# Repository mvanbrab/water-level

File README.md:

# Introduction
Here I share hardware and software about my **water-level** project,
whose purpose is to measure the water level in a water reservoir,
located under the ground.

This project actually has a predecessor. Enjoy reading about it in this [bit of history](doc/history.md).

# The transmitter
The first piece of hardware is a transmitter.
It measures the water level with a waterproof ultrasonic sensor and sends the measurement result as a JSON object via RS232 to a possibly connected receiver.

The positioning of this sensor in my project is described in the [physical setup](doc/physical.md).

Here are some [pictures](doc/pictures-transmitter.md) showing the transmitter in practice.

In the folder **hardware/transmitter** you'll find the hardware design as a [KiCad](https://www.kicad.org/) project.
Without Kicad installed, you can view
- [the schematic diagram as .pdf](../master/hardware/transmitter.pdf);
- [the copper layout of the printed circuit board](../master/hardware/transmitter_cu.pdf);
- [the component placement on the printed circuit board](../master/hardware/transmitter_silk.pdf).

The folder **software/WaterLevelTransmitter** is an [Arduino](https://www.arduino.cc/) sketch, containing the software of the transmitter part of the project.

Read more about this piece of software [here](doc/water-level-transmitter-software.md).

# The receiver
The second piece of hardware is the receiver.
It requests output from the transmitter and publishes is to whatever destination.

Here are some [pictures](doc/pictures-receiver.md) showing the receiver in practice.

In the folder **hardware/receiver** you'll find the hardware design as a [KiCad](https://www.kicad.org/) project.
Without Kicad installed, you can view
- [the schematic diagram as .pdf](../master/hardware/receiver.pdf);
- [the copper layout of the printed circuit board](../master/hardware/receiver_cu.pdf);
- [the component placement on the printed circuit board](../master/hardware/receiver_silk.pdf).

About the receiver hardware:
- the RS232 level converter is the same as used for the transmitter, this time it is powered from 3V3;
- the character-based LCD screen to connect is a 2 rows of 16 columns type, using an HD44780 driver, connected via I2C @ 3V3, but powered @ 5V;
- the processor board (chosen because of its WiFi connectivity) is a [ESP32 DevKitC](https://docs.espressif.com/projects/esp-idf/en/latest/esp32/hw-reference/esp32/get-started-devkitc.html)
 (with ESP32-WROOM-32D module).

The folder **software/WaterLevelReceivers** is contains a set of [Arduino](https://www.arduino.cc/) sketches, each containing a different software solution for the receiver part of the project.

Read more about this piece of software [here](doc/water-level-receiver-software.md).

# Connecting the transmitter with the receiver

| Transmitter | Receiver   |
| ----------- | ---------- |
| GND (J1.2)  | GND (J1.3) |
| TXD (J1.4)  | RXD (J1.2) |
| RXD (J1.5)  | TXD (J1.1) |

# Lessons learned
[The temperature measurement](doc/ll01.md)

[Condensation on the sensor](doc/ll02.md)

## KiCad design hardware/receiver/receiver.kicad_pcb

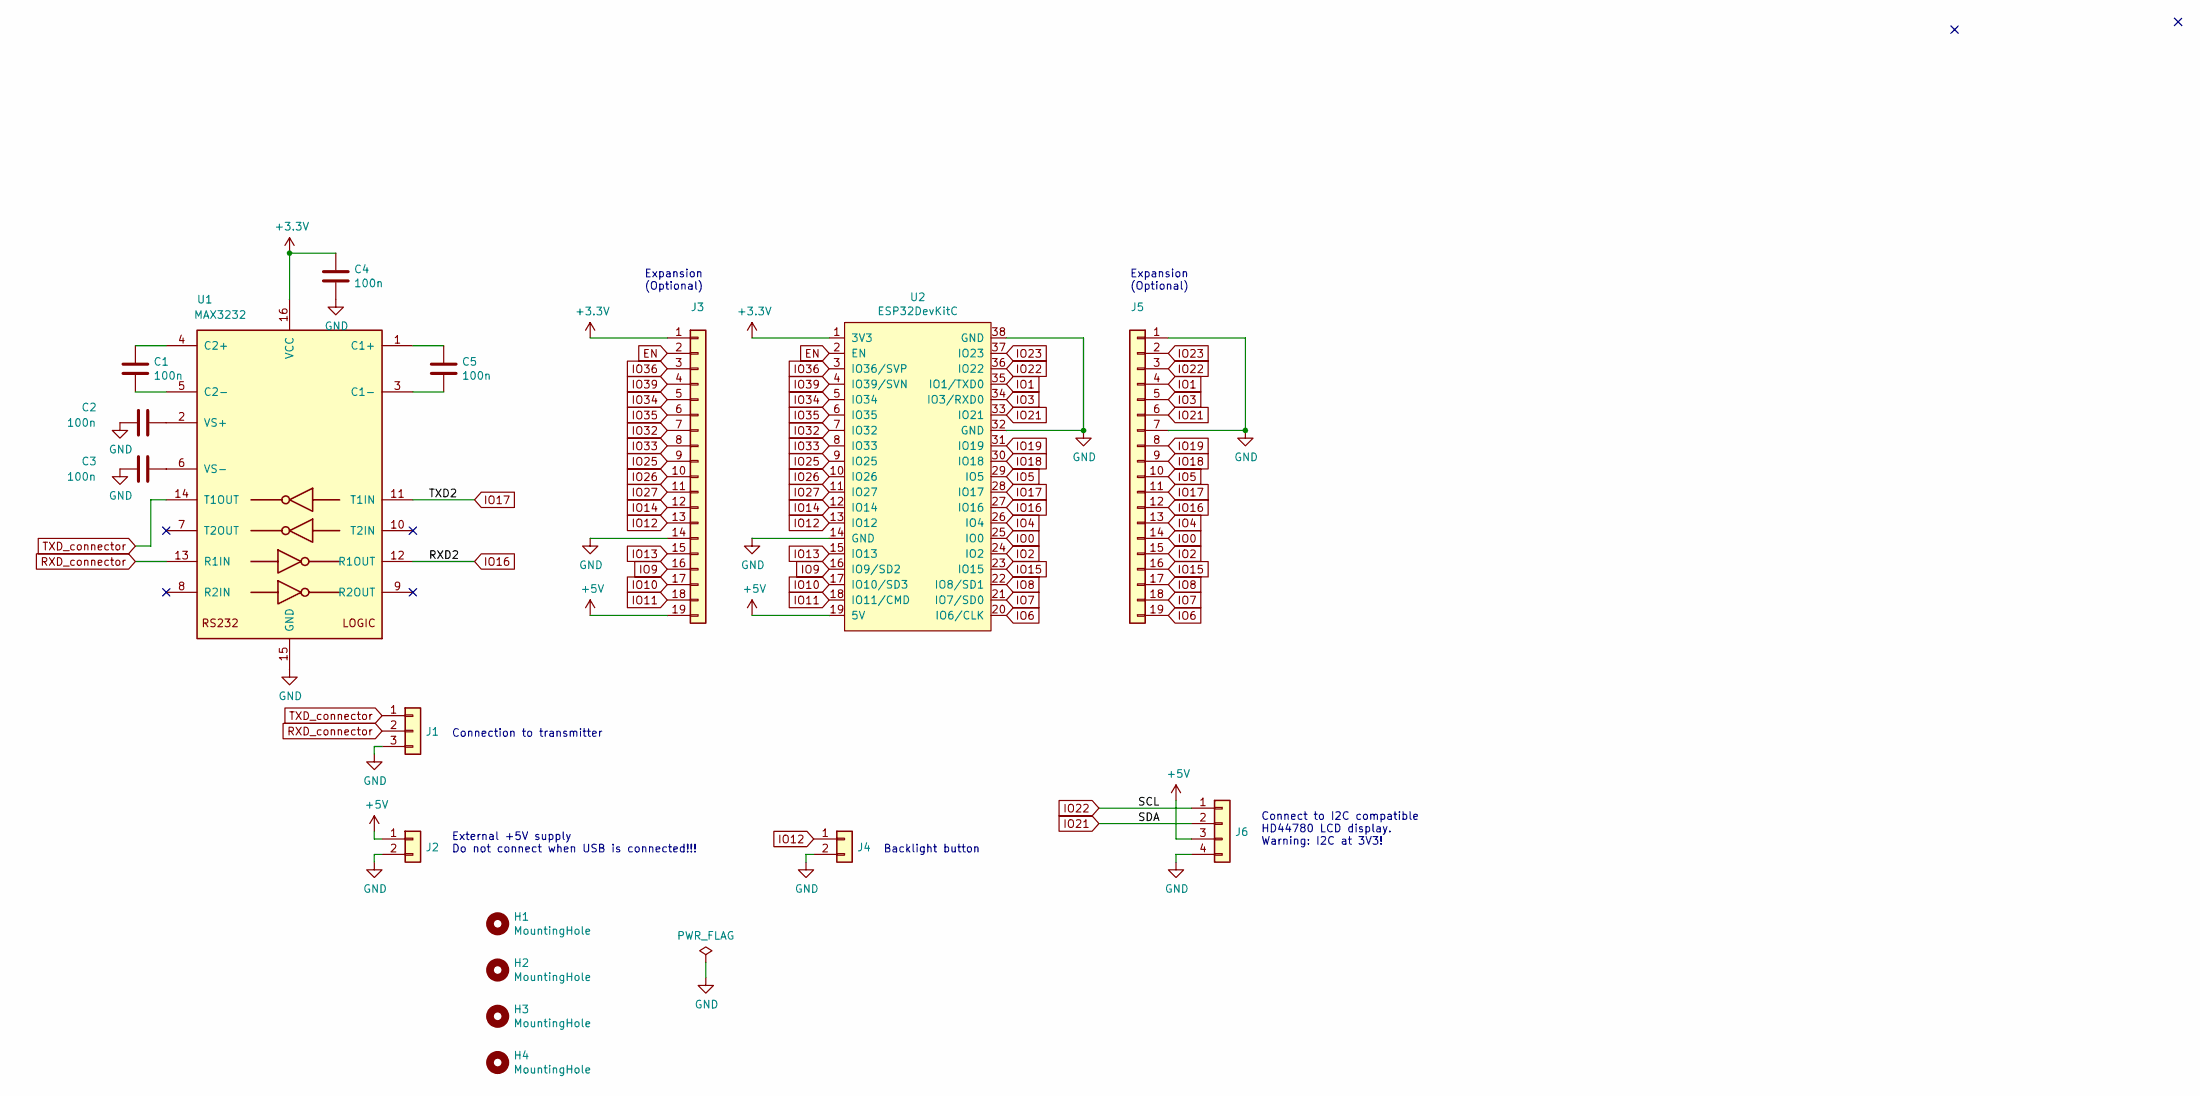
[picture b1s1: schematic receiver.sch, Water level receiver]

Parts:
C1, C2, C3, C4, C5: 100n; C_Rect_L7.0mm_W2.0mm_P5.00mm
H1, H2, H3, H4: MountingHole; MountingHole_3.2mm_M3
J1: Conn_01x03; PinHeader_1x03_P2.54mm_Vertical
J2, J4: Conn_01x02; PinHeader_1x02_P2.54mm_Vertical
J3, J5: Conn_01x19; PinHeader_1x19_P2.54mm_Vertical
J6: Conn_01x04; PinHeader_1x04_P2.54mm_Vertical
U1: MAX3232; DIP-16_W7.62mm_LongPads
U2: ESP32DevKitC; DIP-38_W25.4mm

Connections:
+3V3: C4.1, J3.1, U1.16 (VCC), U2.1 (3V3)
+5V: J2.1, J3.19, J6.3, U2.19 (5V)
EN: J3.2, U2.2 (EN)
GND: C2.2, C3.2, C4.2, J1.3, J2.2, J3.14, J4.2, J5.1, J5.7, J6.4, U1.15 (GND), U2.14 (GND), U2.32 (GND), U2.38 (GND)
IO0: J5.14, U2.25 (IO0)
IO1: J5.4, U2.35 (IO1/TXD0)
IO2: J5.15, U2.24 (IO2)
IO3: J5.5, U2.34 (IO3/RXD0)
IO4: J5.13, U2.26 (IO4)
IO5: J5.10, U2.29 (IO5)
IO6: J5.19, U2.20 (IO6/CLK)
IO7: J5.18, U2.21 (IO7/SD0)
IO8: J5.17, U2.22 (IO8/SD1)
IO9: J3.16, U2.16 (IO9/SD2)
IO10: J3.17, U2.17 (IO10/SD3)
IO11: J3.18, U2.18 (IO11/CMD)
IO12: J3.13, J4.1, U2.13 (IO12)
IO13: J3.15, U2.15 (IO13)
IO14: J3.12, U2.12 (IO14)
IO15: J5.16, U2.23 (IO15)
IO16: J5.12, U1.12 (R1OUT), U2.27 (IO16)
IO17: J5.11, U1.11 (T1IN), U2.28 (IO17)
IO18: J5.9, U2.30 (IO18)
IO19: J5.8, U2.31 (IO19)
IO21: J5.6, J6.2, U2.33 (IO21)
IO22: J5.3, J6.1, U2.36 (IO22)
IO23: J5.2, U2.37 (IO23)
IO25: J3.9, U2.9 (IO25)
IO26: J3.10, U2.10 (IO26)
IO27: J3.11, U2.11 (IO27)
IO32: J3.7, U2.7 (IO32)
IO33: J3.8, U2.8 (IO33)
IO34: J3.5, U2.5 (IO34)
IO35: J3.6, U2.6 (IO35)
IO36: J3.3, U2.3 (IO36/SVP)
IO39: J3.4, U2.4 (IO39/SVN)
unnamed: C1.1, U1.4 (C2+)
unnamed: C1.2, U1.5 (C2-)
unnamed: C2.1, U1.2 (VS+)
unnamed: C3.1, U1.6 (VS-)
unnamed: C5.1, U1.1 (C1+)
unnamed: C5.2, U1.3 (C1-)
RXD_connector: J1.2, U1.13 (R1IN)
TXD_connector: J1.1, U1.14 (T1OUT)

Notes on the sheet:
Connect to I2C compatible HD44780 LCD display. Warning: I2C at 3V3!
External +5V supply Do not connect when USB is connected!!!
Connection to transmitter
Expansion (Optional)
Backlight button

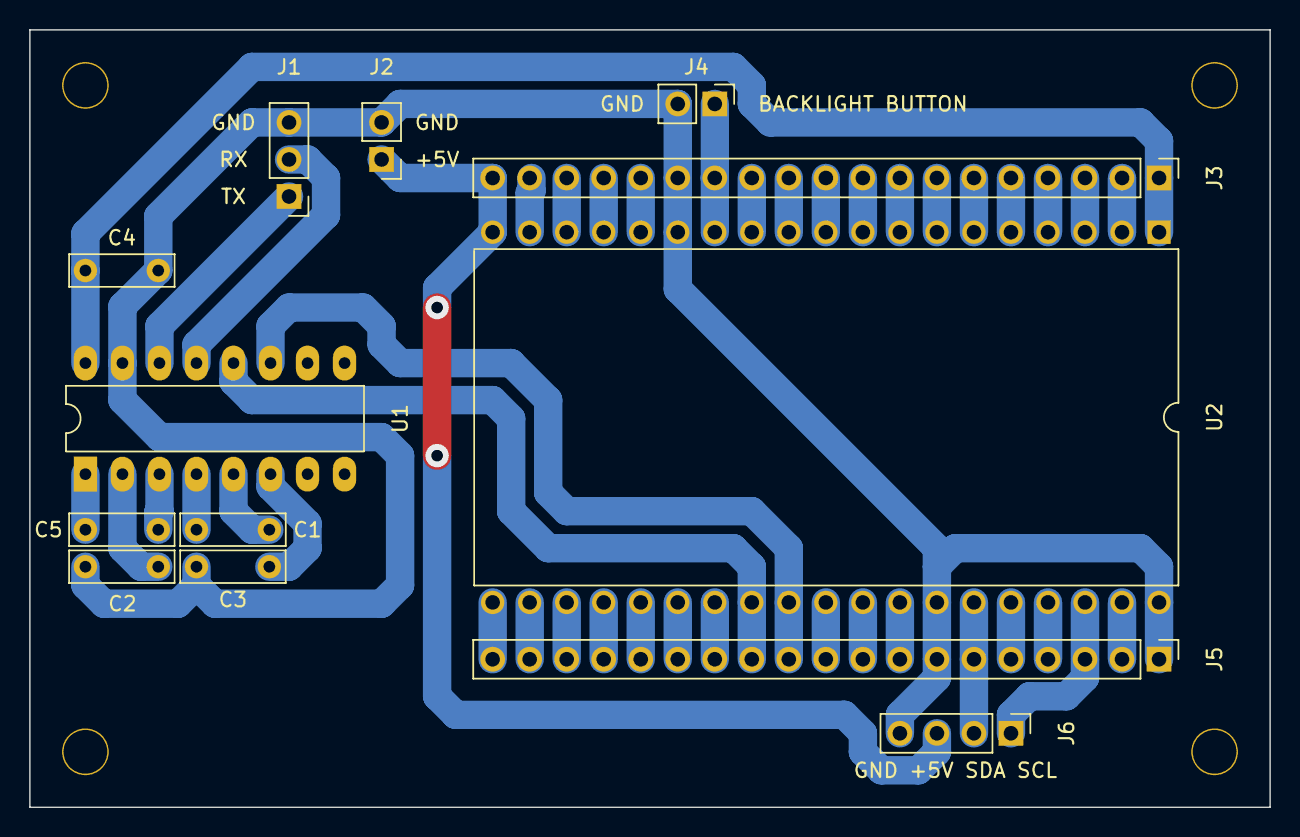
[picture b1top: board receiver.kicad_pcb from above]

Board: 2 copper layers, 85.1 x 53.3 mm, 17 parts (0 on the bottom side), 43 nets.

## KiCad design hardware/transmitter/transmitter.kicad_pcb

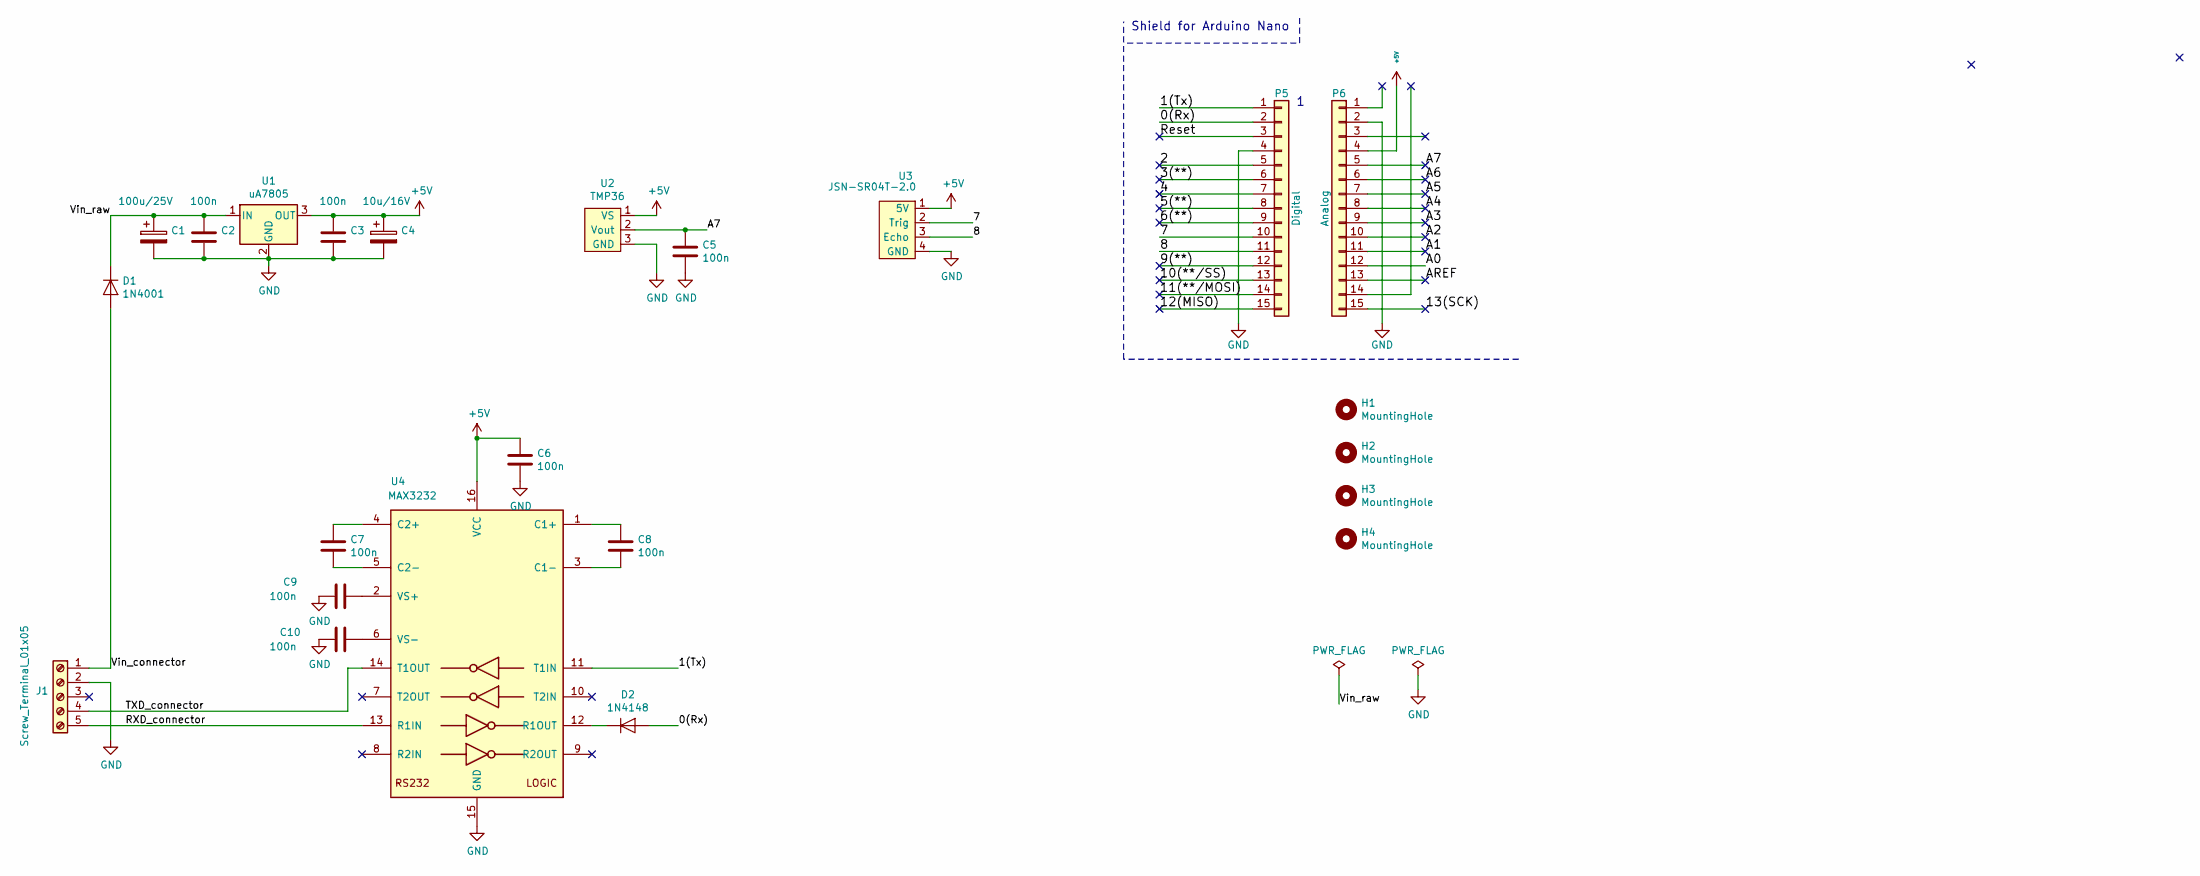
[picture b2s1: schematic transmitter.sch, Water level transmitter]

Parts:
C1: 100u/25V; CP_Radial_D8.0mm_P5.00mm
C2, C3, C5, C6, C7, C8, C9, C10: 100n; C_Rect_L7.0mm_W2.0mm_P5.00mm
C4: 10u/16V; CP_Radial_D8.0mm_P5.00mm
D1: 1N4001; D_DO-41_SOD81_P10.16mm_Horizontal
D2: 1N4148; D_DO-35_SOD27_P7.62mm_Horizontal
H1, H2, H3, H4: MountingHole; MountingHole_3.2mm_M3
J1: Screw_Terminal_01x05; TerminalBlock_MetzConnect_Type101_RT01605HBWC_1x05_P5.08mm_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
P5: Digital; Socket_Strip_Arduino_1x15
P6: Analog; Socket_Strip_Arduino_1x15
U1: uA7805; TO-220-3_Horizontal_TabDown
U2: TMP36; TO-92
U3: JSN-SR04T-2.0; JSN-SR04T-2.0-Vertical
U4: MAX3232; DIP-16_W7.62mm_LongPads

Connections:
+5V: C3.1, C4.1, C6.1, P6.4, U1.3 (OUT), U2.1 (VS), U3.1 (5V), U4.16 (VCC)
/0(Rx): D2.2 (A), P5.2
/1(Tx): P5.1, U4.11 (T1IN)
/2: P5.5
/3(**): P5.6
/4: P5.7
/5(**): P5.8
/6(**): P5.9
/7: P5.10, U3.2 (Trig)
/8: P5.11, U3.3 (Echo)
/9(**): P5.12
/10(**/SS): P5.13
/11(**/MOSI): P5.14
/12(MISO): P5.15
/13(SCK): P6.15
/A0: P6.12
/A1: P6.11
/A2: P6.10
/A3: P6.9
/A4: P6.8
/A5: P6.7
/A6: P6.6
/A7: C5.1, P6.5, U2.2 (Vout)
/AREF: P6.13
/RXD_connector: J1.5, U4.13 (R1IN)
/Reset: P5.3
/TXD_connector: J1.4, U4.14 (T1OUT)
/Vin_connector: D1.2 (A), J1.1
/Vin_raw: C1.1, C2.1, D1.1 (K), U1.1 (IN)
GND: C1.2, C2.2, C3.2, C4.2, C5.2, C6.2, C9.2, C10.2, J1.2, P5.4, P6.2, U1.2 (GND), U2.3 (GND), U3.4 (GND), U4.15 (GND)
unnamed: C7.1, U4.4 (C2+)
unnamed: C7.2, U4.5 (C2-)
unnamed: C8.1, U4.1 (C1+)
unnamed: C8.2, U4.3 (C1-)
unnamed: C9.1, U4.2 (VS+)
unnamed: C10.1, U4.6 (VS-)
unnamed: D2.1 (K), U4.12 (R1OUT)

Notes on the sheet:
Shield for Arduino Nano

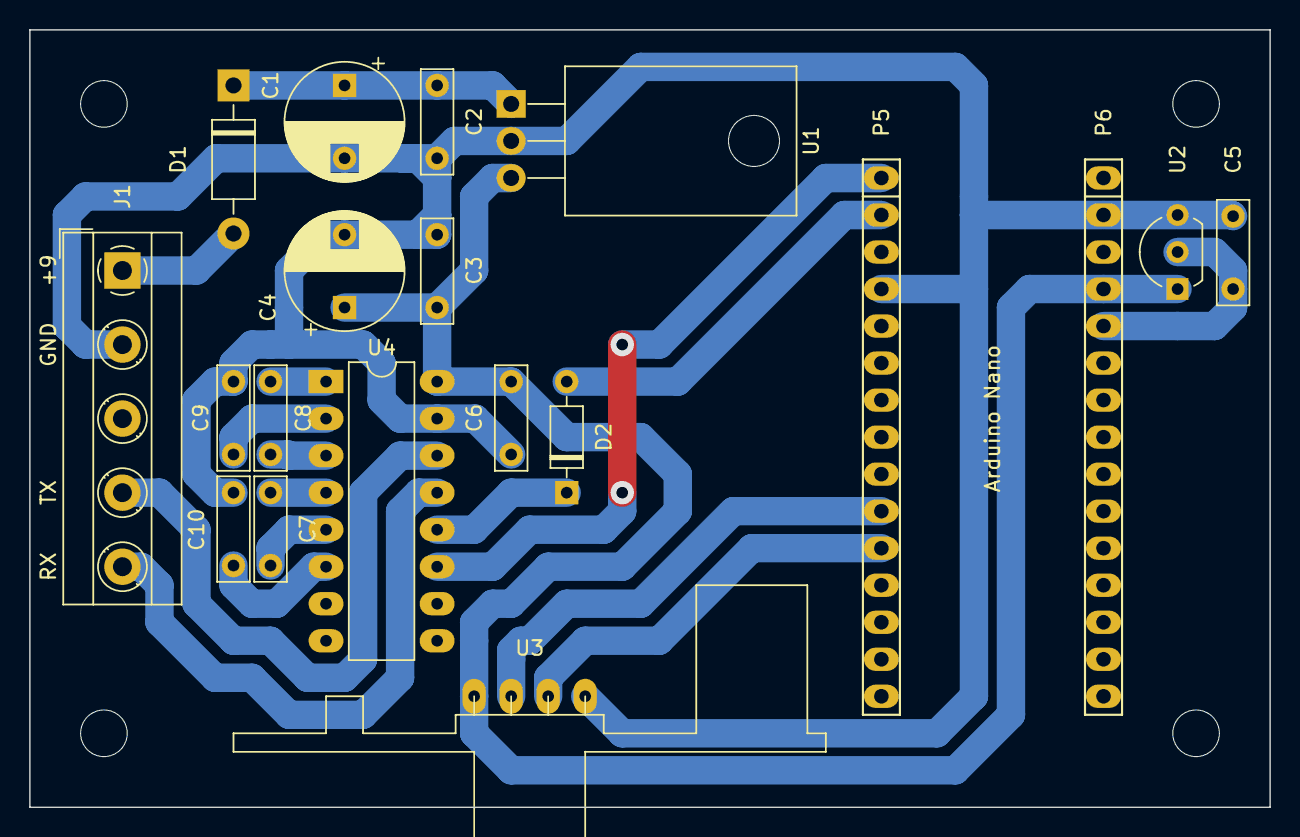
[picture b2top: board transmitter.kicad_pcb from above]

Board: 2 copper layers, 85.1 x 53.3 mm, 23 parts (0 on the bottom side), 18 nets.

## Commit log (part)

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2020-03-03 first commit of transmitter
2020-03-03 added copper zone
2020-03-07 added plot_files
2020-03-08 added software/WaterLevelTransmitter
2020-03-08 added documentation
2020-03-08 added dimensions
2020-03-08 Corrected link
2020-03-09 copper zone reviewed (clearance, minimum with, solid pad connection)
2020-03-14 updated documentation and transmitter constant names
2020-03-14 typos etc.
2020-03-21 moved transmitter.pdf
2020-04-27 pcb narrowed by 5 mm
2020-05-17 typo
2020-05-17 WaterLevelReceiver: first commit (debug output only)
2020-05-24 resized board to 85,090 mm x 53,340 mm
2020-05-30 Add GCode files for LinuxCNC PCB milling and PCB sticker
2020-06-05 improved silk + additional .pdfs
2020-06-05 cleanup after accepting pull request
2020-06-07 ADD: "History"
2020-06-07 ADD: images
2020-06-20 WaterLevelReceiver with serial and LCD output
2020-06-21 changed layout on LCD
2020-06-21 extended documentation
2020-06-21 Documentation fixes
2020-06-22 averaging the input for smoother display
2020-06-23 smoothing, doc, buffer overflow
2020-06-24 Added output to ThingSpeak
2020-06-24 added lessons learned
2020-06-24 update ThingSpeak status at every write
2020-06-25 lessons learned: temperature measurement (solution)
2020-06-25 lessons learned: temperature measurement (pictures)
2020-06-25 lessons learned: temperature measurement
2020-06-25 publish in floating point unless local override
2020-06-25 publish ThingSpeak: also volume in liters
2020-07-04 added backlight button
2020-07-06 refactored receiver sketch
2020-07-06 refactored receiver sketch (2)
2020-07-10 added receiver
2020-07-10 transmitter.pdf in color
2020-07-16 Receiver, ThingSpeak output: LOW moved from status to field 4
2020-07-18 UPD: thingspeak-output.jpg
2020-08-09 ADD: receiver PCB, connections transmitter-receiver
2020-08-09 UPD: doc/thingspeak-output.jpg
2020-08-30 ADD: receiver box pictures
2020-11-10 ADD: current issue 1.
2020-11-10 UPD: current issue 1.
2020-11-15 ADD: solution for condensation (under evaluation)
2020-11-15 CHG: distance parameter H3
2020-12-29 DEL: ThingSpeak output; ADD: MQTT output
2021-01-02 ADD: doc: Node-RED flow MQTT --> ThingSpeak
2021-02-15 More output examples using MQTT and Node-RED
2021-03-07 update on condensation issue
2021-04-05 update current issue 1
2021-04-10 new H3 after changing position of sensor
2021-04-11 Condensation issue: attempt 3
2021-11-10 Update README.md
    https://forum.kicad.info/t/warning-avoid-all-links-to-kicad-pcb-org-use-kicad-org/31521
2022-05-13 condensation on the sensor: from current issue to lesson learned
2022-05-13 Copied pictures to pictures-transmitter.md
2024-04-28 Documentation header update
2024-05-15 MQTT conditionally compiled
2024-05-19 first HTTP version
2024-05-20 finished HTTP version; destinations compile-time selectable
2024-08-22 build with Arduino IDE 2.3.2 and esp32 board manager 3.0.3
2024-11-29 new receivers working, except mqtt
2024-11-29 @file
2024-11-30 LCDMQTT is working
2024-11-30 doc update
2024-12-16 doc cleanup
2024-12-16 Split receivers and updated documentation (#3)
2026-05-19 rounded mqtt output
2026-06-08 version bump of Arduino IDE and esp32 board manager/libraries
2026-06-09 change MQTT topic to home/regenput/state
2026-06-12 Added MQTT Discovery messages with single component discovery payload
